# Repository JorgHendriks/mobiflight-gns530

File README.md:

# GNS 530 Flight-Simulator GPS

A DIY Garmin GNS 530-inspired panel for flight simulation, designed for use with [MobiFlight](https://www.mobiflight.com/). The project includes a Raspberry Pi Pico, custom PCB, a 5-inch LCD, a printed and laser-engraved enclosure, Mobiflight configuration.

> [!IMPORTANT]
> This is an unofficial hobby project for flight simulation. It is not certified
> for aviation use and is not affiliated with or endorsed by Garmin.

## Features

- COM/VLOC and GPS dual-concentric encoders
- Illuminated GNS 530 controls
- 5-inch 640 x 480 display with HDMI, VGA, and composite-video input
- Adjustable panel illumination
- Editable KiCad and FreeCAD sources
- Printable parts, laser artwork, schematic, BOM, and PCB fabrication files

## Repository contents

| Folder | Contents |
|---|---|
| [`pcb`](pcb) | KiCad source, schematic, BOM, fabrication archive, display references, and assembly notes |
| [`mechanical`](mechanical) | FreeCAD source, printable parts, hardware, painting, and laser settings |
| [`mobiflight`](mobiflight) | Pico module configuration and Microsoft Flight Simulator project |

## What you need

- The components in the [PCB bill of materials](pcb/README.md#bill-of-materials)
- The printed parts and GNS530-specific [mounting hardware](mechanical/README.md#hardware)
- PCB800099 video controller and ZJ050NA-08C 5-inch LCD
- 12 V DC power supply rated above 1 A for the video controller
- Raspberry Pi Pico, MobiFlight

## Build documentation

1. Manufacture and assemble the board using the [PCB guide](pcb).
2. Print, paint, engrave, and assemble the enclosure using the
   [mechanical guide](mechanical).
3. Use the official MobiFlight documentation for
   [board configurations](https://docs.mobiflight.com/features/file-types/),
   [projects](https://docs.mobiflight.com/features/projects/), and
   [controller bindings](https://docs.mobiflight.com/features/controller-bindings/).

The supplied MobiFlight files are [`GNS530.mfmc`](mobiflight/GNS530.mfmc) and
[`GNS530.mfproj`](mobiflight/GNS530.mfproj).

## Licence

Original project material is licensed under
[CC BY-NC-SA 4.0](https://creativecommons.org/licenses/by-nc-sa/4.0/).
Third-party material and trademarks remain the property of their owners.

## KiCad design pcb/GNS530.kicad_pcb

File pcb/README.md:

# PCB

## PCB manufacturing

The ready-to-order fabrication archive is
[`GNS530_v1_1_pcb_fab.zip`](GNS530_v1_1_pcb_fab.zip). Use a standard board
thickness of **1.6 mm**.

- [KiCad project](GNS530.kicad_pro)
- [Schematic PDF](GNS530_schematic.pdf)

The local symbol and footprint libraries are referenced through `${KIPRJMOD}`.

## Bill of materials

| Designators | Qty | Component | Specification |
|---|---:|---|---|
| RE_GPS1, RE_COM_VLOC1 | 2 | Dual-concentric encoder | PEC11D-4120F-S0015 |
| Q2 | 1 | P-channel MOSFET | AO3401A, SOT-23 |
| C1 | 1 | Capacitor | 0.1 uF, 1206 |
| R1-R23, R32-R36 | 28 | Resistor | 220 ohm, 1206 |
| R24-R31, R39, R40 | 10 | Resistor | 10 kohm, 1206 |
| Q1 | 1 | NPN transistor | BC847, SOT-23 |
| SW_CDI1, SW_CLR1, SW_COM1, SW_DCT1, SW_ENT1, SW_FPL1, SW_MENU1, SW_MSG1, SW_OBS1, SW_PROC1, SW_RNG_D1, SW_RNG_UP1, SW_V1, SW_VNAV1 | 14 | Illuminated tactile switch | 6 x 6 x 7.2 mm, six pins |
| D1-D14 | 14 | LED | 3 mm clear through-hole |
| U1 | 1 | Shift register | 74HC165, SOIC-16 |
| RE_VOL_COM1, RE_VOL_V1 | 2 | Rotary encoder with switch | PEC11L-4220F-S0015 |
| EXT_LED1 | 1 | Two-pin header | 2.54 mm pitch |
| A1 | 1 | Microcontroller | Raspberry Pi Pico |
| - | 2 | Male pin header | 20 pins, 2.54 mm pitch |
| - | 2 | Female socket header | 20 pins, 2.54 mm pitch |

## Illuminated switches

Use 6 x 6 x 7.2 mm, six-pin illuminated tactile switches. Four pins form the
duplicated switch contacts; the remaining two connect the LED.

The small square PCB pad is ground and connects to the negative LED terminal.

## Display

The enclosure is designed for a **PCB800099** HDMI/VGA/AV controller and
**ZJ050NA-08C** 5-inch 640 x 480 LCD.

| Part | Specification |
|---|---|
| PCB800099 controller | 100 x 55 x 10 mm; 12 V DC, more than 1 A |
| ZJ050NA-08C LCD | 117.65 x 88.43 x 5.9 mm; 50-pin parallel RGB |

- [Controller dimensions](../mechanical/display/PCB800099_dimensions.png)
- [Controller datasheet](../mechanical/display/PCB800099_datasheet.pdf)
- [LCD datasheet](../mechanical/display/ZJ050NA-08C_datasheet.pdf)
- [Controller product image](../mechanical/display/PCB800099_product.jpg)

The display controller uses its own 12 V supply. Do not connect 12 V to the Pico or the LCD panel input.

If your controller board includes VGA and composite-video connectors, desolder
them before assembly. Alternatively, modify the back cover to provide adequate
clearance for the connectors.

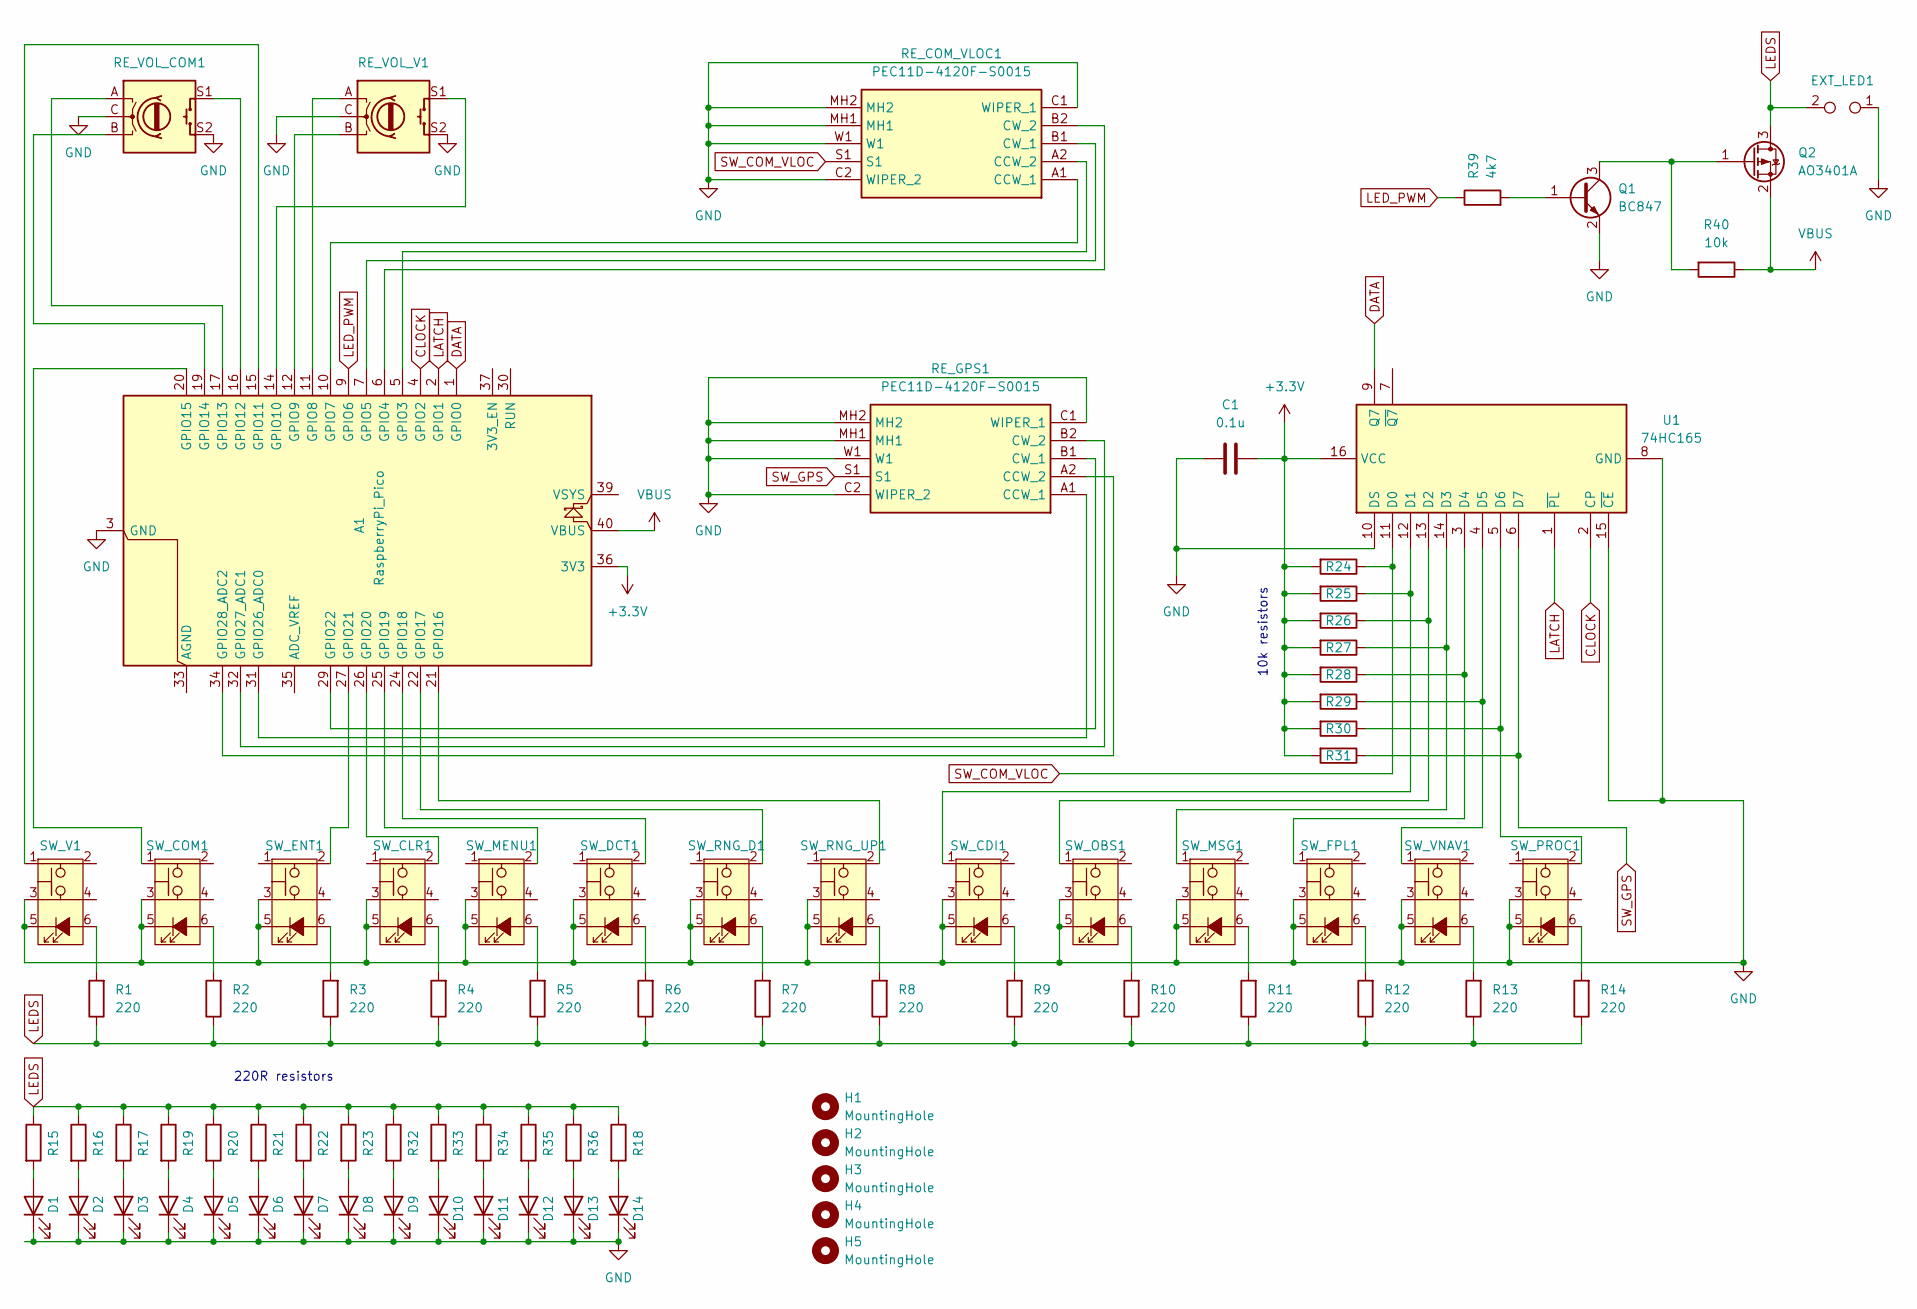
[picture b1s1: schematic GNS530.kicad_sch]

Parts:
A1: RaspberryPi_Pico; RaspberryPi_Pico_Common_Unspecified
C1: 0.1u; R_1206_3216Metric
D1, D2, D3, D4, D5, D6, D7, D8, D9, D10, D11, D12, D13, D14: LED; LED_D3.0mm_Clear
EXT_LED1: TestPoint_2Pole; PinHeader_2x01_P2.54mm_Vertical
H1, H2, H3, H4, H5: MountingHole; MountingHole_2.2mm_M2
Q1: BC847; SOT-23
Q2: AO3401A; SOT-23
R1, R2, R3, R4, R5, R6, R7, R8, R9, R10, R11, R12, R13, R14, R15, R16, R17, R18, R19, R20, R21, R22, R23, R32, R33, R34, R35, R36: 220; R_1206_3216Metric
R24, R25, R26, R27, R28, R29, R30, R31, R40: 10k; R_1206_3216Metric
R39: 4k7; R_1206_3216Metric
RE_COM_VLOC1: PEC11D-4120F-S0015; PEC11D4120FS0015; Mouser Part Number 652-PEC11D4120FS0015
RE_GPS1: PEC11D-4120F-S0015; PEC11D4120FS0015; Mouser Part Number 652-PEC11D4120FS0015
RE_VOL_COM1: RotaryEncoder_Switch; RotaryEncoder_Alps_EC11E-Switch_Vertical_H20mm
RE_VOL_V1: RotaryEncoder_Switch; RotaryEncoder_Alps_EC11E-Switch_Vertical_H20mm
SW_CDI1: SW_Push_LED_6p; SW_PUSH_LED_6mm_H7.2mm
SW_CLR1: SW_Push_LED_6p; SW_PUSH_LED_6mm_H7.2mm
SW_COM1: SW_Push_LED_6p; SW_PUSH_LED_6mm_H7.2mm
SW_DCT1: SW_Push_LED_6p; SW_PUSH_LED_6mm_H7.2mm
SW_ENT1: SW_Push_LED_6p; SW_PUSH_LED_6mm_H7.2mm
SW_FPL1: SW_Push_LED_6p; SW_PUSH_LED_6mm_H7.2mm
SW_MENU1: SW_Push_LED_6p; SW_PUSH_LED_6mm_H7.2mm
SW_MSG1: SW_Push_LED_6p; SW_PUSH_LED_6mm_H7.2mm
SW_OBS1: SW_Push_LED_6p; SW_PUSH_LED_6mm_H7.2mm
SW_PROC1: SW_Push_LED_6p; SW_PUSH_LED_6mm_H7.2mm
SW_RNG_D1: SW_Push_LED_6p; SW_PUSH_LED_6mm_H7.2mm
SW_RNG_UP1: SW_Push_LED_6p; SW_PUSH_LED_6mm_H7.2mm
SW_V1: SW_Push_LED_6p; SW_PUSH_LED_6mm_H7.2mm
SW_VNAV1: SW_Push_LED_6p; SW_PUSH_LED_6mm_H7.2mm
U1: 74HC165; JEITA_SOIC-16_3.9x9.9mm_P1.27mm

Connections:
+3.3V: A1.36 (3V3), C1.2, R24.2, R25.2, R26.2, R27.2, R28.2, R29.2, R30.2, R31.2, U1.16 (VCC)
CLOCK: A1.4 (GPIO2), U1.2 (CP)
DATA: A1.1 (GPIO0), U1.9 (Q7)
GND: A1.3 (GND), A1.8 (GND), A1.13 (GND), A1.18 (GND), A1.23 (GND), A1.28 (GND), A1.38 (GND), C1.1, D1.1 (K), D2.1 (K), D3.1 (K), D4.1 (K), D5.1 (K), D6.1 (K), D7.1 (K), D8.1 (K), D9.1 (K), D10.1 (K), D11.1 (K), D12.1 (K), D13.1 (K), D14.1 (K), EXT_LED1.1, Q1.2 (E), RE_COM_VLOC1.C1 (WIPER_1), RE_COM_VLOC1.C2 (WIPER_2), RE_COM_VLOC1.MH1, RE_COM_VLOC1.MH2, RE_COM_VLOC1.W1, RE_GPS1.C1 (WIPER_1), RE_GPS1.C2 (WIPER_2), RE_GPS1.MH1, RE_GPS1.MH2, RE_GPS1.W1, RE_VOL_COM1.C, RE_VOL_COM1.S2, RE_VOL_V1.C, RE_VOL_V1.S2, SW_CDI1.3, SW_CDI1.5 (K), SW_CLR1.3, SW_CLR1.5 (K), SW_COM1.3, SW_COM1.5 (K), SW_DCT1.3, SW_DCT1.5 (K), SW_ENT1.3, SW_ENT1.5 (K), SW_FPL1.3, SW_FPL1.5 (K), SW_MENU1.3, SW_MENU1.5 (K), SW_MSG1.3, SW_MSG1.5 (K), SW_OBS1.3, SW_OBS1.5 (K), SW_PROC1.3, SW_PROC1.5 (K), SW_RNG_D1.3, SW_RNG_D1.5 (K), SW_RNG_UP1.3, SW_RNG_UP1.5 (K), SW_V1.3, SW_V1.5 (K), SW_VNAV1.3, SW_VNAV1.5 (K), U1.8 (GND), U1.10 (DS), U1.15 (~CE)
LATCH: A1.2 (GPIO1), U1.1 (~PL)
LEDS: EXT_LED1.2, Q2.3 (D), R1.1, R2.1, R3.1, R4.1, R5.1, R6.1, R7.1, R8.1, R9.1, R10.1, R11.1, R12.1, R13.1, R14.1, R15.1, R16.1, R17.1, R18.1, R19.1, R20.1, R21.1, R22.1, R23.1, R32.1, R33.1, R34.1, R35.1, R36.1
LED_PWM: A1.9 (GPIO6), R39.1
unnamed: A1.5 (GPIO3), RE_COM_VLOC1.A2 (CCW_2)
unnamed: A1.6 (GPIO4), RE_COM_VLOC1.B2 (CW_2)
unnamed: A1.7 (GPIO5), RE_COM_VLOC1.B1 (CW_1)
unnamed: A1.10 (GPIO7), RE_COM_VLOC1.A1 (CCW_1)
unnamed: A1.11 (GPIO8), RE_VOL_V1.A
unnamed: A1.12 (GPIO9), RE_VOL_V1.B
unnamed: A1.14 (GPIO10), RE_VOL_V1.S1
unnamed: A1.15 (GPIO11), SW_V1.1
unnamed: A1.16 (GPIO12), RE_VOL_COM1.S1
unnamed: A1.17 (GPIO13), RE_VOL_COM1.A
unnamed: A1.19 (GPIO14), RE_VOL_COM1.B
unnamed: A1.20 (GPIO15), SW_COM1.1
unnamed: A1.21 (GPIO16), SW_RNG_UP1.2
unnamed: A1.22 (GPIO17), SW_RNG_D1.2
unnamed: A1.24 (GPIO18), SW_DCT1.2
unnamed: A1.25 (GPIO19), SW_MENU1.2
unnamed: A1.26 (GPIO20), SW_CLR1.2
unnamed: A1.27 (GPIO21), SW_ENT1.2
unnamed: A1.29 (GPIO22), RE_GPS1.B1 (CW_1)
unnamed: A1.31 (GPIO26_ADC0), RE_GPS1.A1 (CCW_1)
unnamed: A1.32 (GPIO27_ADC1), RE_GPS1.B2 (CW_2)
unnamed: A1.34 (GPIO28_ADC2), RE_GPS1.A2 (CCW_2)
unnamed: D1.2 (A), R15.2
unnamed: D2.2 (A), R16.2
unnamed: D3.2 (A), R17.2
unnamed: D4.2 (A), R19.2
unnamed: D5.2 (A), R20.2
unnamed: D6.2 (A), R21.2
unnamed: D7.2 (A), R22.2
unnamed: D8.2 (A), R23.2
unnamed: D9.2 (A), R32.2
unnamed: D10.2 (A), R33.2
unnamed: D11.2 (A), R34.2
unnamed: D12.2 (A), R35.2
unnamed: D13.2 (A), R36.2
unnamed: D14.2 (A), R18.2
unnamed: Q1.1 (B), R39.2
unnamed: Q1.3 (C), Q2.1 (G), R40.2
unnamed: R1.2, SW_V1.6
unnamed: R2.2, SW_COM1.6
unnamed: R3.2, SW_ENT1.6
unnamed: R4.2, SW_CLR1.6
unnamed: R5.2, SW_MENU1.6
unnamed: R6.2, SW_DCT1.6
unnamed: R7.2, SW_RNG_D1.6
unnamed: R8.2, SW_RNG_UP1.6
unnamed: R9.2, SW_CDI1.6
unnamed: R10.2, SW_OBS1.6
unnamed: R11.2, SW_MSG1.6
unnamed: R12.2, SW_FPL1.6
unnamed: R13.2, SW_VNAV1.6
unnamed: R14.2, SW_PROC1.6
unnamed: R25.1, SW_CDI1.1, U1.12 (D1)
unnamed: R26.1, SW_OBS1.1, U1.13 (D2)
unnamed: R27.1, SW_MSG1.1, U1.14 (D3)
unnamed: R28.1, SW_FPL1.1, U1.3 (D4)
unnamed: R29.1, SW_VNAV1.1, U1.4 (D5)
unnamed: R30.1, SW_PROC1.2, U1.5 (D6)
SW_COM_VLOC: R24.1, RE_COM_VLOC1.S1, U1.11 (D0)
SW_GPS: R31.1, RE_GPS1.S1, U1.6 (D7)
VBUS: A1.40 (VBUS), Q2.2 (S), R40.1

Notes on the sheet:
10k resistors
220R resistors

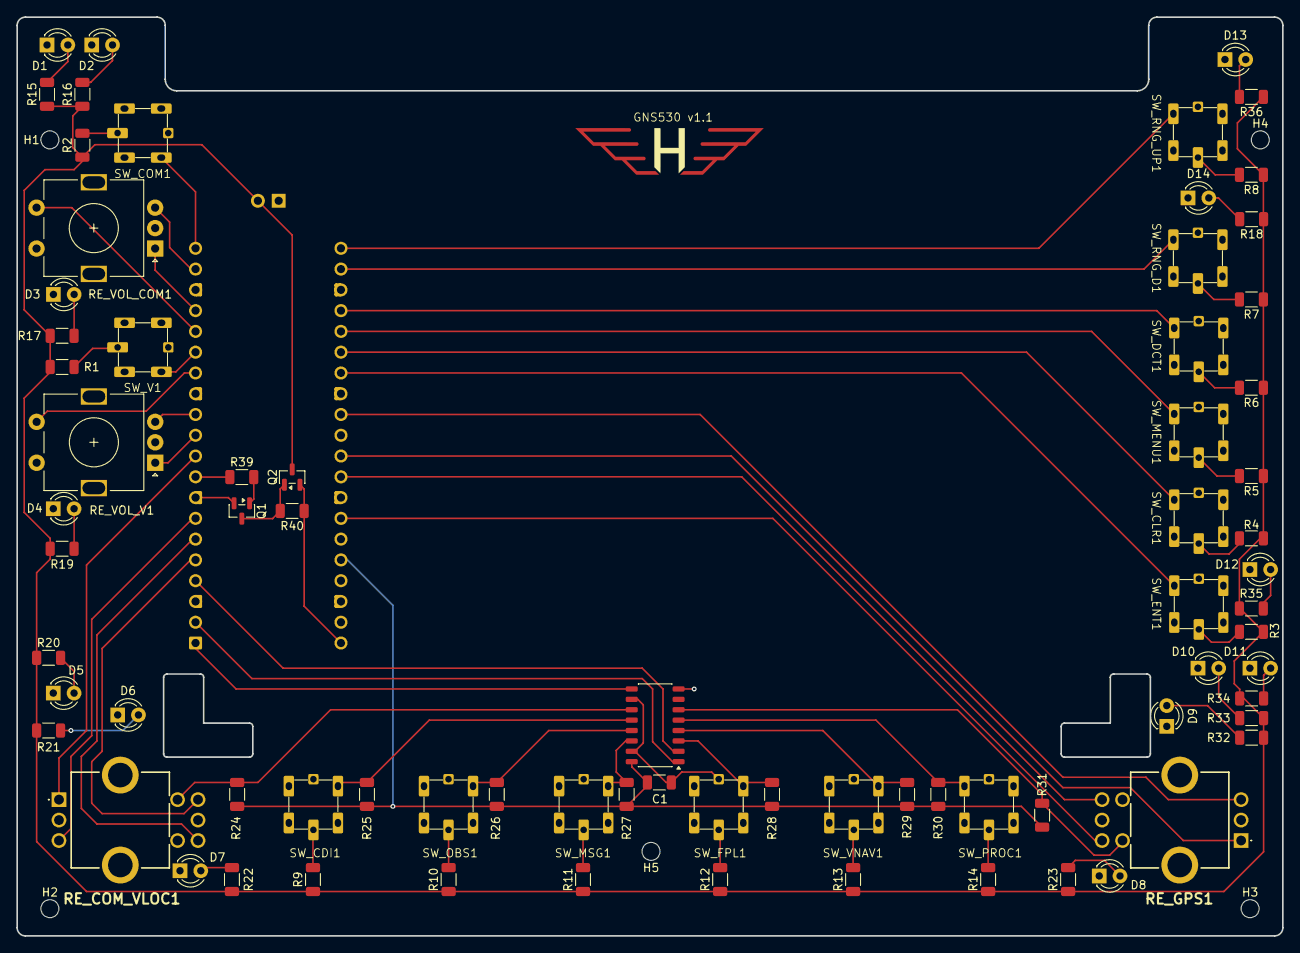
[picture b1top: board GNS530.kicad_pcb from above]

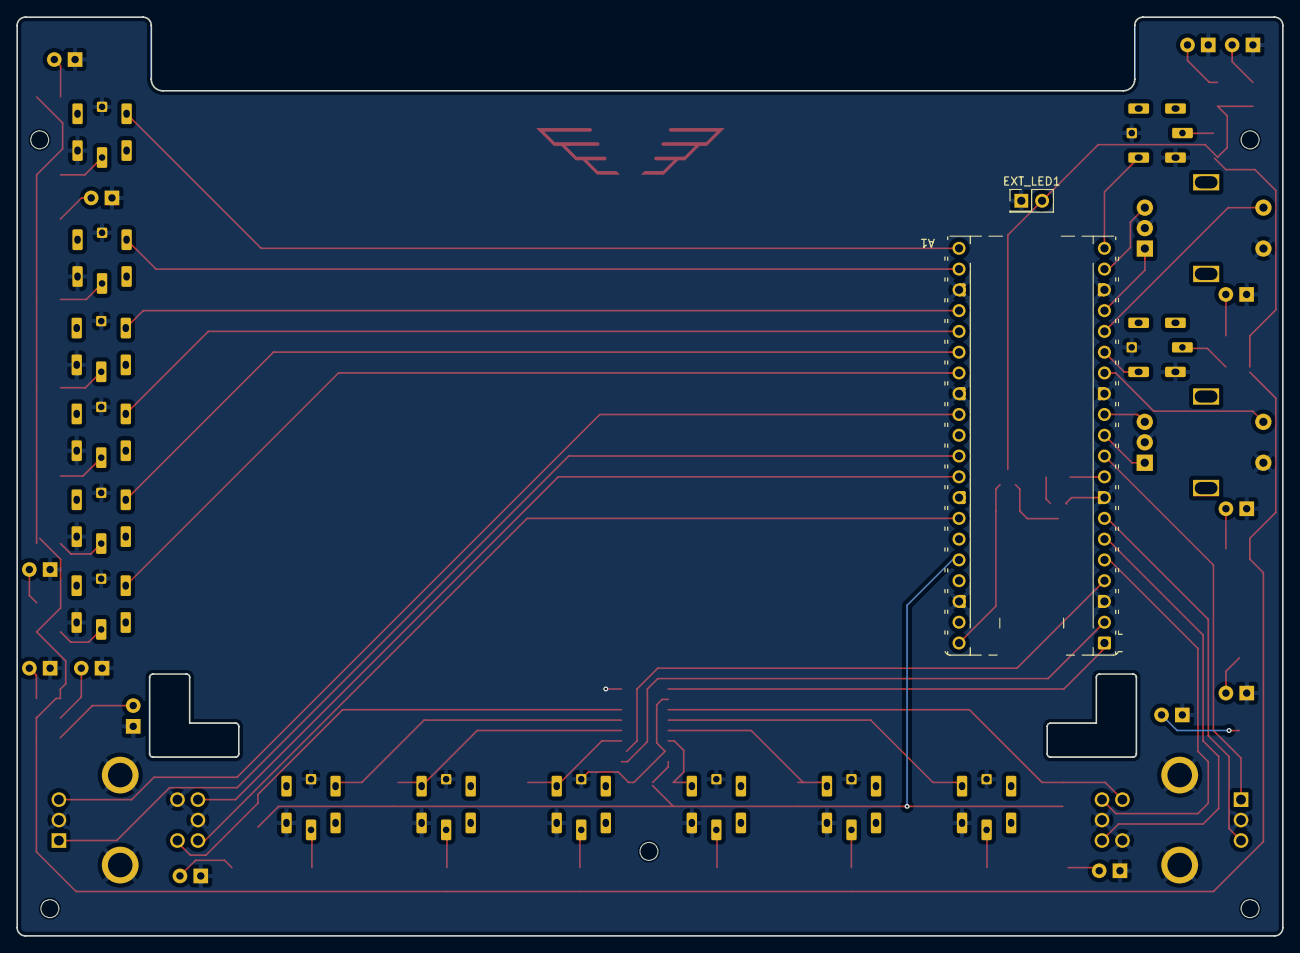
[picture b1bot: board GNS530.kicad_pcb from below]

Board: 2 copper layers, 154.8 x 112.3 mm, 81 parts (2 on the bottom side), 68 nets.
